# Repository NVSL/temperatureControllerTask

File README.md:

# Temperature Controller Task

You have the task of building a temperature controller system that will eventually replace my old line of controllers for [glass door coolers](http://tor-rey-refrigeration.com/glass-door-coolers/). You will develop the temperature controller using two different web tools: Amalgam and Appliancizer.

## Temperature Controller Software 
The temperature controller software is provided in ```Your_Name/amalgamApp/app.html```

## Building the Temperature Controller with Amalgam (Measure the time you spent writing the CSS and building the Eagle PCB spearately)

After checking the ```app.html``` code it's time to indicate to the Amalgam tool which HTML elements you want them to be physical. The physcial electrical components will interact with a raspberry Pi 2/3/4 connector. 

From the HTML elements in ```app.html``` only the temperature text must remain. All other HTML elements must be physical. Follow the following list:    
1.-  __\<div\>__ text that shows the temperature in Celsius (e.g., 25°C). (Must remain on Screen)     
2.- __\<input\>__ temperature sensor input slider with range from -40°C to +125°C. (Must be a physical temp sensor)      
3.- __\<button\>__ temperature set point up (+1 °C). (Must be a physical button)   
4.- __\<button\>__ temperature set point down (-1 °C). (Must be a physical button)   
5.- __\<span\>__ text that will show "ON" if the temperature is greater than the temperature set point, else "OFF". (Must be a physical led)   

**FIRST TASK (CSS):** Add to the ```hardware.css``` file located in ```Your_Name/amalgamApp/``` the required hardware css selectors needed by Amalgam and that match the list above, follow the examples.   
    
Example 1: HTML button to physical button. 
```html
<!-- example.html -->
<button id="myInput"> BUTTON TEXT </button>
```
```css
/* hardware.css */
#myInput {
  hardware: physical-button(gpio:4);
}
```

Example 2: HTML Input slider to physcial i2c potentiometer
```html
<!-- example.html -->
<input type="range" id="mySensor" min="0" max="10" step="1" value="0">
```
```css
/* hardware.css */
#mySensor {
  hardware: physical-pot(i2c-port:url("/dev/i2c-1"), i2c-addr:0x40);
}
```

Is your task to figure out the electrical component name tag (e.g., physical-button) and required values (e.g, gpio:4) to use for a raspberry Pi connector. Use the following list to choose the correct electrical component name.

```css
#<YourElementId> {
  hardware: <electrical component name tag> (required value 1, requred value 2, ...);
}
```

| Electrical component name tag | Required values                                                                                                        | Electrical component Examples   |
|---------------------------|------------------------------------------------------------------------------------------------------------------------|---------------------------------|
| physical-button           | gpio:<gpio_number>)                                                                                     | Push buttons, 1-bit Inputs      |
| physical-output           | gpio:<gpio_number>)                                                                                     | Leds, 1-bit Outputs             |
| physical-pot              | adc-channel: "<1,2,3 or 4>" <br> i2c-port:url("<i2c_port_path>") <br> i2c-addr:0x40                                                                         | Potentiometer using ADS1011 ADC |
| physical-rgb-led          | spi-port:url("<spi_port_path>")                                                                                        | SPI RGB LEDs                    |
| physical-servo-motor      | servo-channel: "<1,2,3 or 4>" <br> i2c-port:url("<spi_port_path>") <br> i2c-addr: 0x40                                          | I2C Servo motors                |
| physical-motorized-pot    | motora:<gpio_number> <br> motorb:"<gpio_number>" <br> touch:<gpio_number> <br> i2c-addr:0x48 <br> i2c-port:url("<i2c_port_path>") | I2C Motorized Potentiometer     |
| physical-temp-sensor      | i2c-port:url("<i2c_port_path>") <br> i2c-addr:0x18                                                                         | I2C Temperature sensor          |

| AVAILABLE RPI PORTS | PORT PATH  | GPIO Number |
| ----------| ----------------| ------------ |
| i2c       | "/dev/i2c-1"    | SDA: 2, SCL: 3 |
| spi       | "/dev/spidev0.0"| MOSI: 10, MISO: 9, SCLK: 11, CE0: 8 |
| serial    | "/dev/ttyS0"    | TXD: 14, RXD: 15 |
| gpio      |     N/A            | 4, 17, 27, 22, 5, 6, 13, 26, 18, 23, 24, 25, 12, 16, 19, 20, 21 |   

[raspberry pinout image](https://roboticsbackend.com/wp-content/uploads/2019/05/raspberry-pi-3-pinout-768x810.jpg)

**SECOND TASK (EAGLE):** 

For the second task you must make a PCB that will connect to a Raspberry Pi 40-pin connector. You will require a temperature sensor, two buttons, and a led. All eagle parts are provided in ```Your_Name/eaglePCB/tempControllerParts.lbr```. Connections must match the port paths and gpio numbers in the ```hardware.css``` file.    

Save your schematic (\*.sch) board (\*sch) and gerber files in ```Your_Name/amalgamApp/eaglePCB```. 

## Building the Temperature Controller with Appliancizer (Measure the time you spent using appliancizer until you download the PCB)

Appliancizer website: https://appliancizer.com/    
- Add the temperature software code using the "ADD WEB PAGE+" Button, then click "INJECT". 
- Choose any screen size.
- Drag and Drop Components to the PCB area following the list provided in the Amalgam section. 
- Click "Build", then click "Generate PCB File" and save the generated zip files in ```Your_Name/amalgamApp/applaincizerZip```.    

## ---
Finally commit: Your ```hardware.css``` file, PCB files (.sch, .brd, gerber files) and the generated Amalgam zip to the repo. Send me an email when you push your work and also send me your times. 

| TASK | TIMES |
| ----------| ----------------|
| Devon       |  |
| Amalgam, first taks  | 6 minutes | 
| Amalgam, second task | 15 minutes 30 seconds + 10 minutes to do gerbers (I'm not sure I did the gerbers right. Also not sure I did the pull up resistors right, because I'm not sure which pins are NC/NO on the button.) | 
| Appliancizer         | 4 minutes 30 seconds |  
| Steve       |  |
| Amalgam, first taks  | 7:37 | 
| Amalgam, second task | 14:16 | 
| Appliancizer         | 3:39 |

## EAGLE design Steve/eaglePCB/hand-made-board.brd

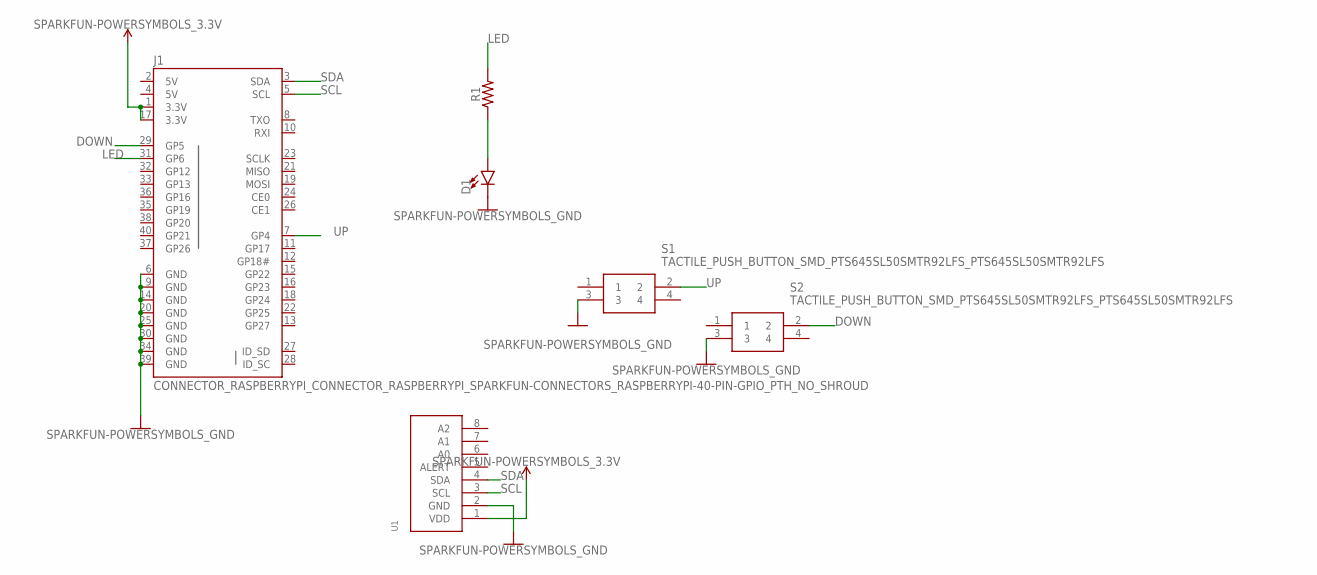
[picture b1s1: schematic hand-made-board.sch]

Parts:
D1: LED_SMD_SPARKFUN-LED_LED1206; LED_SMD_SPARKFUN-LED_LED-1206
J1: CONNECTOR_RASPBERRYPI_CONNECTOR_RASPBERRYPI_SPARK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; CONNECTOR_RASPBERRYPI_CONNECTOR_RASPBERRYPI_SPARKFUN-CONNEC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
R1: LED_SMD_SPARKFUN-RESISTORS_1206
S1, S2: TACTILE_PUSH_BUTTON_SMD_PTS645SL50SMTR92LFS_PTS64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; TACTILE_PUSH_BUTTON_SMD_PTS645SL50SMTR92LFS_PTS645SMT
U1: TEMPERATURE_SENSOR_MCP9808

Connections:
3.3V: J1.1 (3.3V), J1.17 (3.3V), U1.1 (VDD)
5V: J1.2 (5V), J1.4 (5V)
DOWN: J1.29 (GP5), S2.2
GND: D1.C, J1.6 (GND), J1.9 (GND), J1.14 (GND), J1.20 (GND), J1.25 (GND), J1.30 (GND), J1.34 (GND), J1.39 (GND), S1.3, S2.3, U1.2 (GND)
LED: J1.31 (GP6), R1.2
unnamed: D1.A, R1.1
SCL: J1.5 (SCL), U1.3 (SCL)
SDA: J1.3 (SDA), U1.4 (SDA)
UP: J1.7 (GP4), S1.2

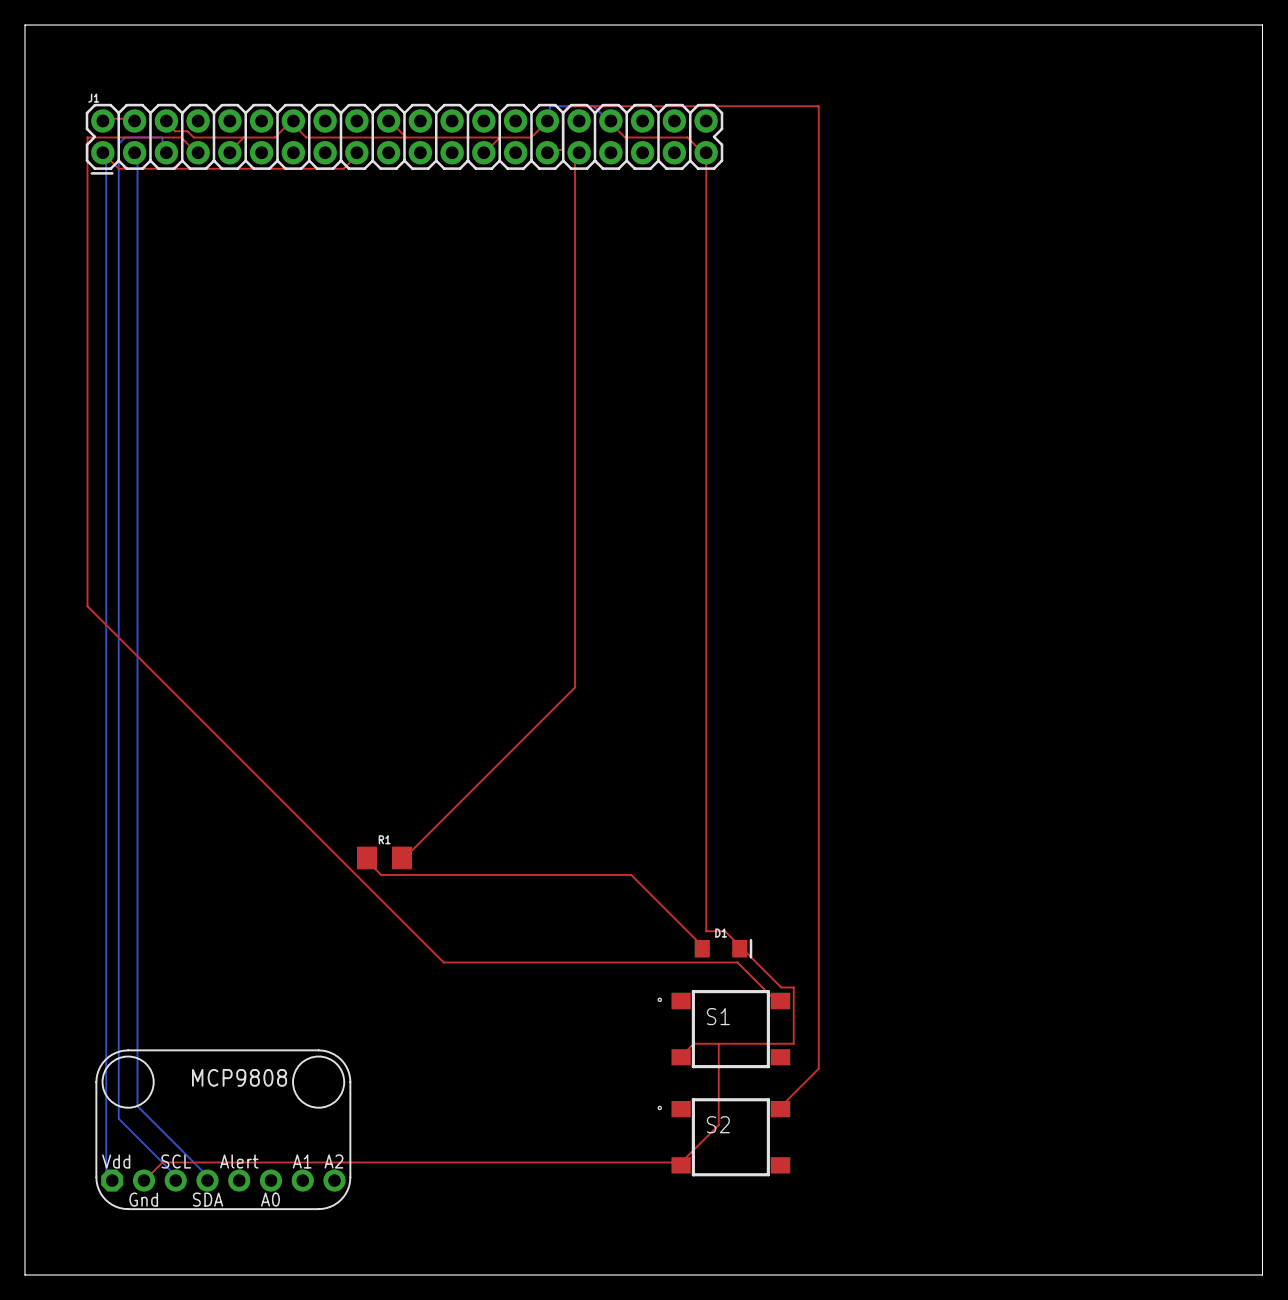
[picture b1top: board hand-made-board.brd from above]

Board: 2 copper layers, 99.0 x 100.0 mm, 6 parts (0 on the bottom side), 9 nets.

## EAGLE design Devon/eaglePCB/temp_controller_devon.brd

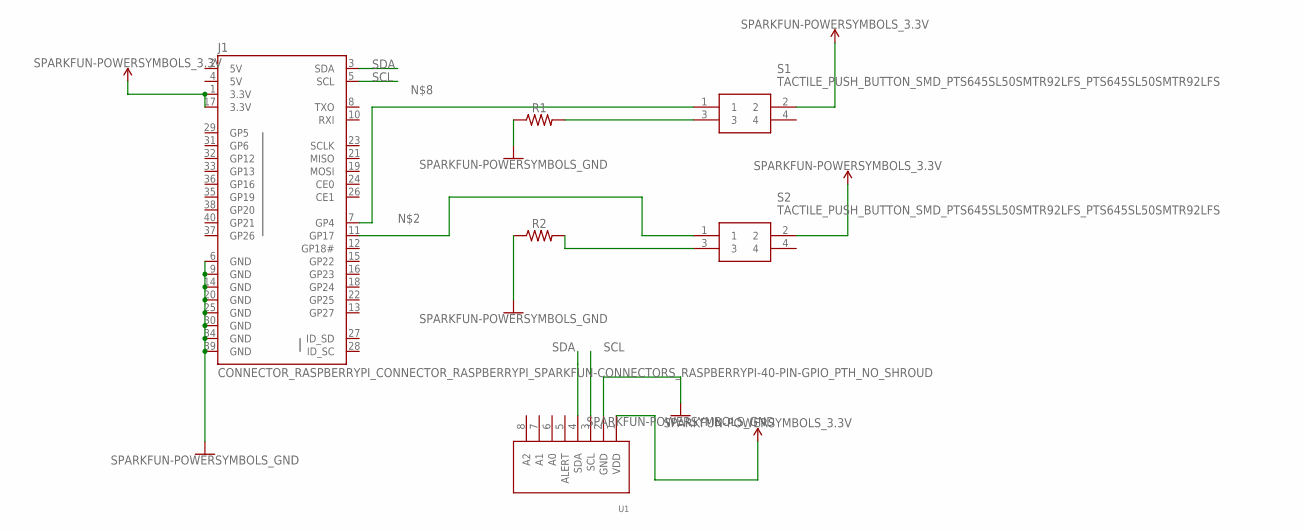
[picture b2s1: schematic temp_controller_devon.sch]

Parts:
J1: CONNECTOR_RASPBERRYPI_CONNECTOR_RASPBERRYPI_SPARK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; CONNECTOR_RASPBERRYPI_CONNECTOR_RASPBERRYPI_SPARKFUN-CONNEC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
R1, R2: LED_SMD_SPARKFUN-RESISTORS_1206
S1, S2: TACTILE_PUSH_BUTTON_SMD_PTS645SL50SMTR92LFS_PTS64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; TACTILE_PUSH_BUTTON_SMD_PTS645SL50SMTR92LFS_PTS645SMT
U1: TEMPERATURE_SENSOR_MCP9808

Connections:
3.3V: J1.1 (3.3V), J1.17 (3.3V), S1.2, S2.2, U1.1 (VDD)
5V: J1.2 (5V), J1.4 (5V)
GND: J1.6 (GND), J1.9 (GND), J1.14 (GND), J1.20 (GND), J1.25 (GND), J1.30 (GND), J1.34 (GND), J1.39 (GND), R1.1, R2.1, U1.2 (GND)
unnamed: J1.11 (GP17), S2.1
unnamed: R2.2, S2.3
unnamed: R1.2, S1.3
unnamed: J1.7 (GP4), S1.1
SCL: J1.5 (SCL), U1.3 (SCL)
SDA: J1.3 (SDA), U1.4 (SDA)

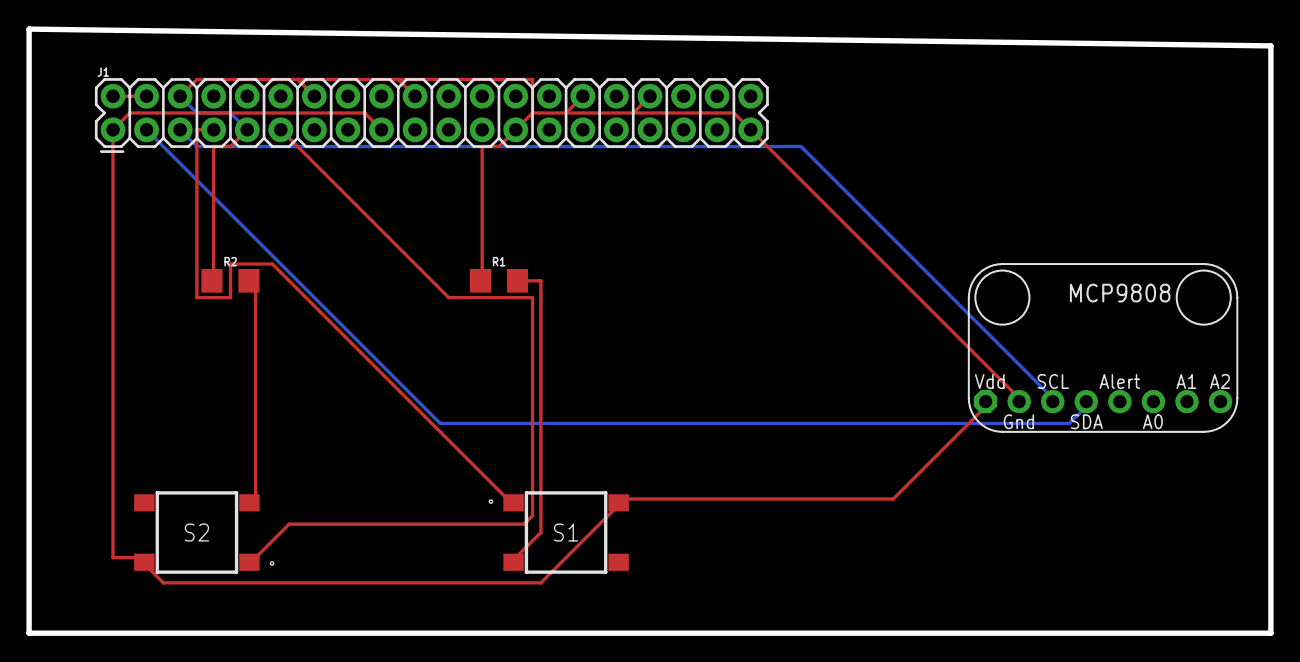
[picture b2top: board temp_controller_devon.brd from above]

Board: 2 copper layers, 94.0 x 45.7 mm, 6 parts (0 on the bottom side), 9 nets.

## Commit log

2020-04-18 Adding Folders
2020-04-18 Adding appliancizer Folder
2020-04-23 Adding all needed Ealge parts
2020-04-23 Adding Temp Controller Code
2020-04-28 Update hardware.css
    Hardware style
2020-04-29 Steve's version
